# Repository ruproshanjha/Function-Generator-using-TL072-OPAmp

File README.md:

# Function-Generator-using-TL072-OPAmp

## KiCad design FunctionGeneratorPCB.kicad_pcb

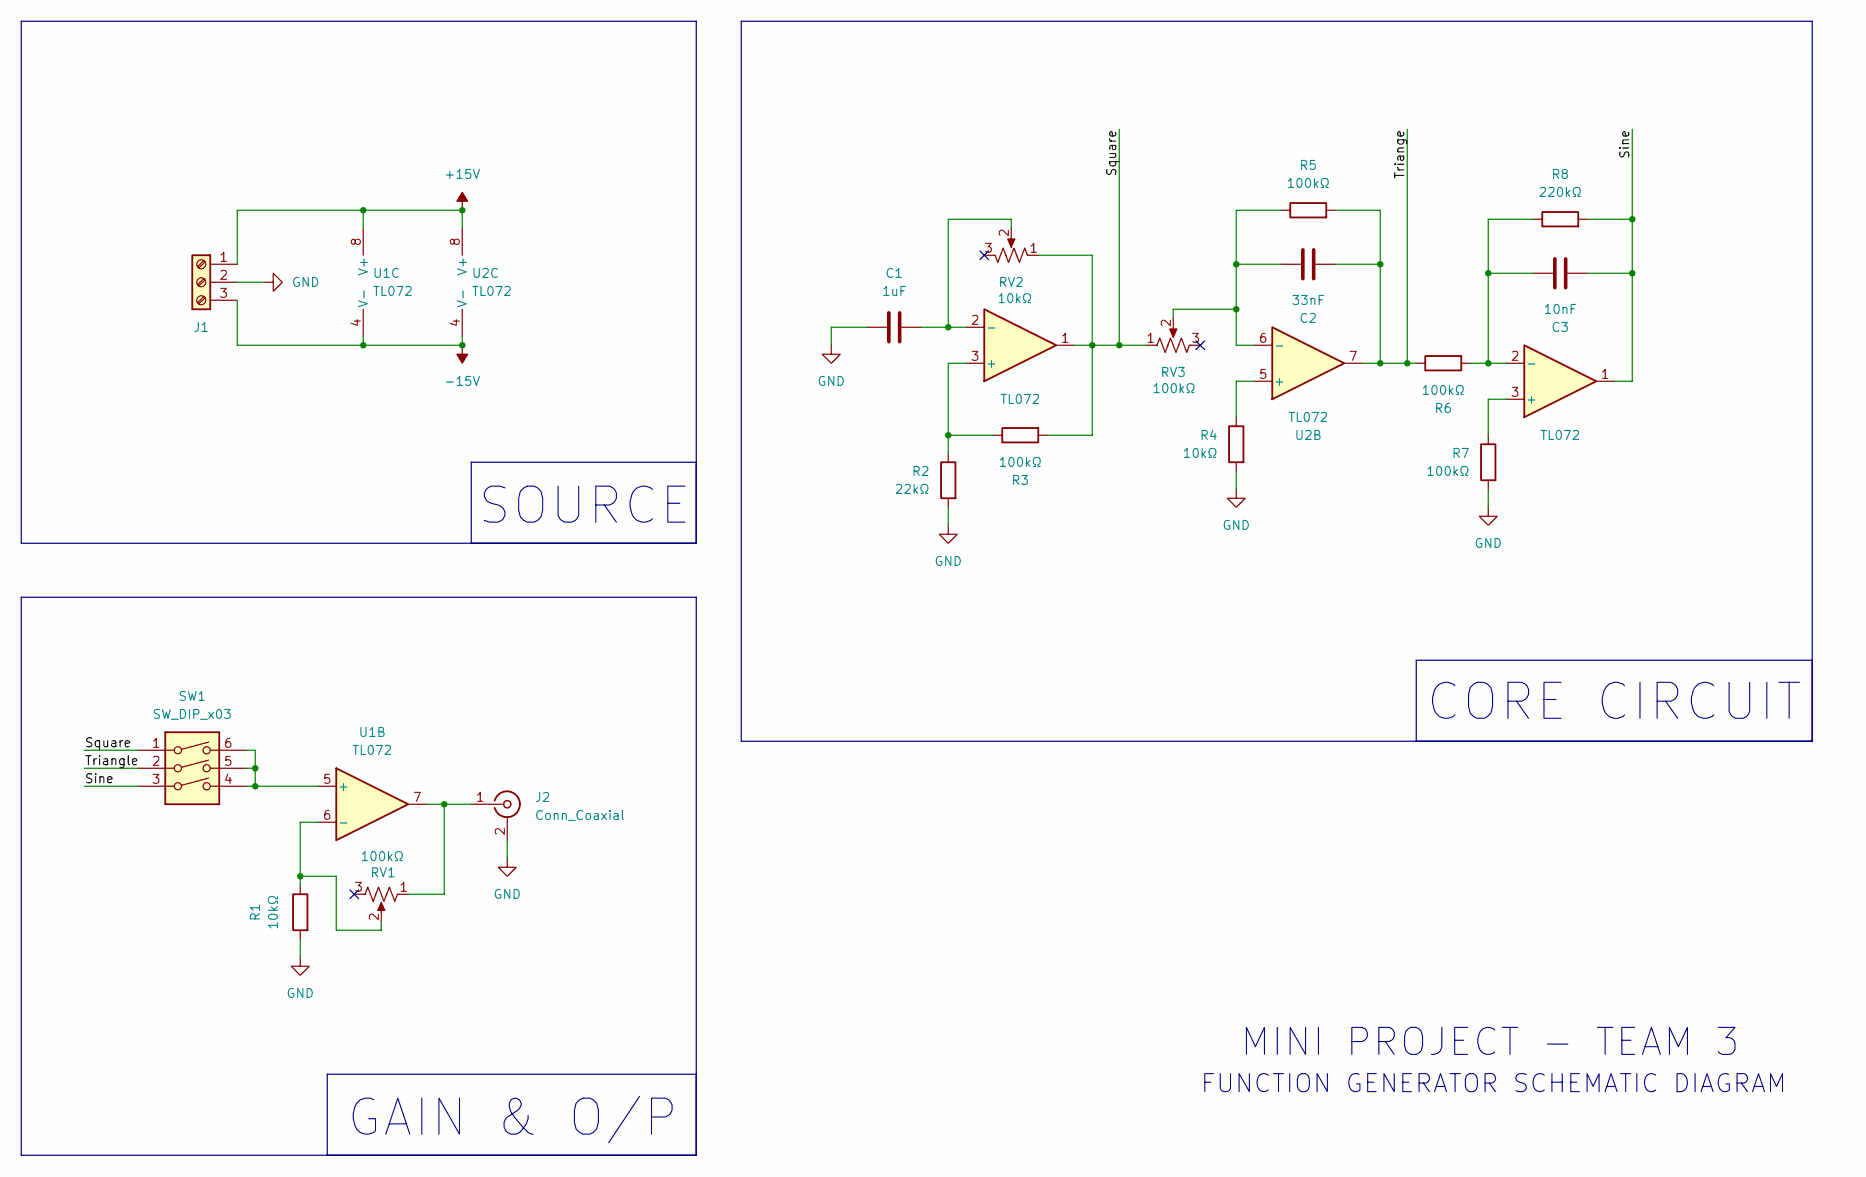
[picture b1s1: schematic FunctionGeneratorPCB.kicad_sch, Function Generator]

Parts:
C1: 1uF; C_Disc_D3.4mm_W2.1mm_P2.50mm
C2: 33nF; C_Disc_D3.4mm_W2.1mm_P2.50mm
C3: 10nF; C_Disc_D3.4mm_W2.1mm_P2.50mm
J1: Screw_Terminal_01x03; Altech_AK300_1x03_P5.00mm_45-Degree
J2: Conn_Coaxial; BNC_Amphenol_B6252HB-NPP3G-50_Horizontal
R1, R4: 10kΩ; R_Axial_DIN0207_L6.3mm_D2.5mm_P10.16mm_Horizontal
R2: 22kΩ; R_Axial_DIN0207_L6.3mm_D2.5mm_P10.16mm_Horizontal
R3, R5, R6, R7: 100kΩ; R_Axial_DIN0207_L6.3mm_D2.5mm_P10.16mm_Horizontal
R8: 220kΩ; R_Axial_DIN0207_L6.3mm_D2.5mm_P10.16mm_Horizontal
RV1, RV3: 100kΩ; POT_PTN16-A100125K1B1
RV2: 10kΩ; POT_PTN16-A100125K1B1
SW1: SW_DIP_x03; SW_DIP_SPSTx03_Slide_6.7x9.18mm_W7.62mm_P2.54mm_LowProfile
U1, U2: TL072

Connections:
+15V: J1.1, U1.8 (V+), U2.8 (V+)
-15V: J1.3, U1.4 (V-), U2.4 (V-)
/Sine: C3.2, R8.2, SW1.3, U2.1
/Square: R3.2, RV2.1, RV3.1, SW1.1, U1.1
/Triange: C2.2, R5.2, R6.1, U2.7
/Triangle: SW1.2
GND: C1.1, J1.2, J2.2 (Ext), R1.2, R2.2, R4.2, R7.2
unnamed: J2.1 (In), RV1.1, U1.7
unnamed: R2.1, R3.1, U1.3 (+)
unnamed: C1.2, RV2.2, U1.2 (-)
unnamed: SW1.4, SW1.5, SW1.6, U1.5 (+)
unnamed: R1.1, RV1.2, U1.6 (-)
unnamed: R7.1, U2.3 (+)
unnamed: C3.1, R6.2, R8.1, U2.2 (-)
unnamed: R4.1, U2.5 (+)
unnamed: C2.1, R5.1, RV3.2, U2.6 (-)

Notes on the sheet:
FUNCTION GENERATOR SCHEMATIC DIAGRAM
MINI PROJECT - TEAM 3
SOURCE
CORE CIRCUIT
GAIN & O/P

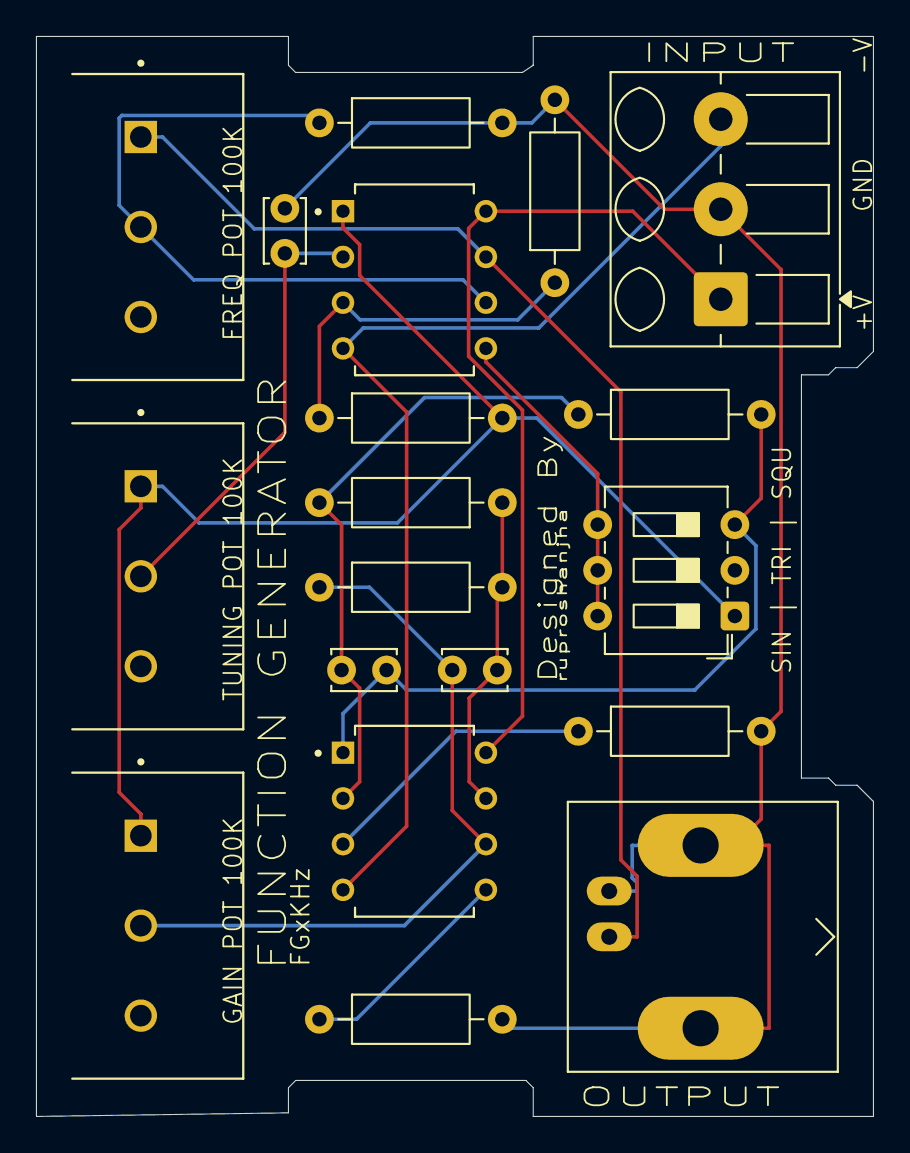
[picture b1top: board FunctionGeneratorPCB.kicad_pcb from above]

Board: 2 copper layers, 46.5 x 60.0 mm, 19 parts (0 on the bottom side), 15 nets.
